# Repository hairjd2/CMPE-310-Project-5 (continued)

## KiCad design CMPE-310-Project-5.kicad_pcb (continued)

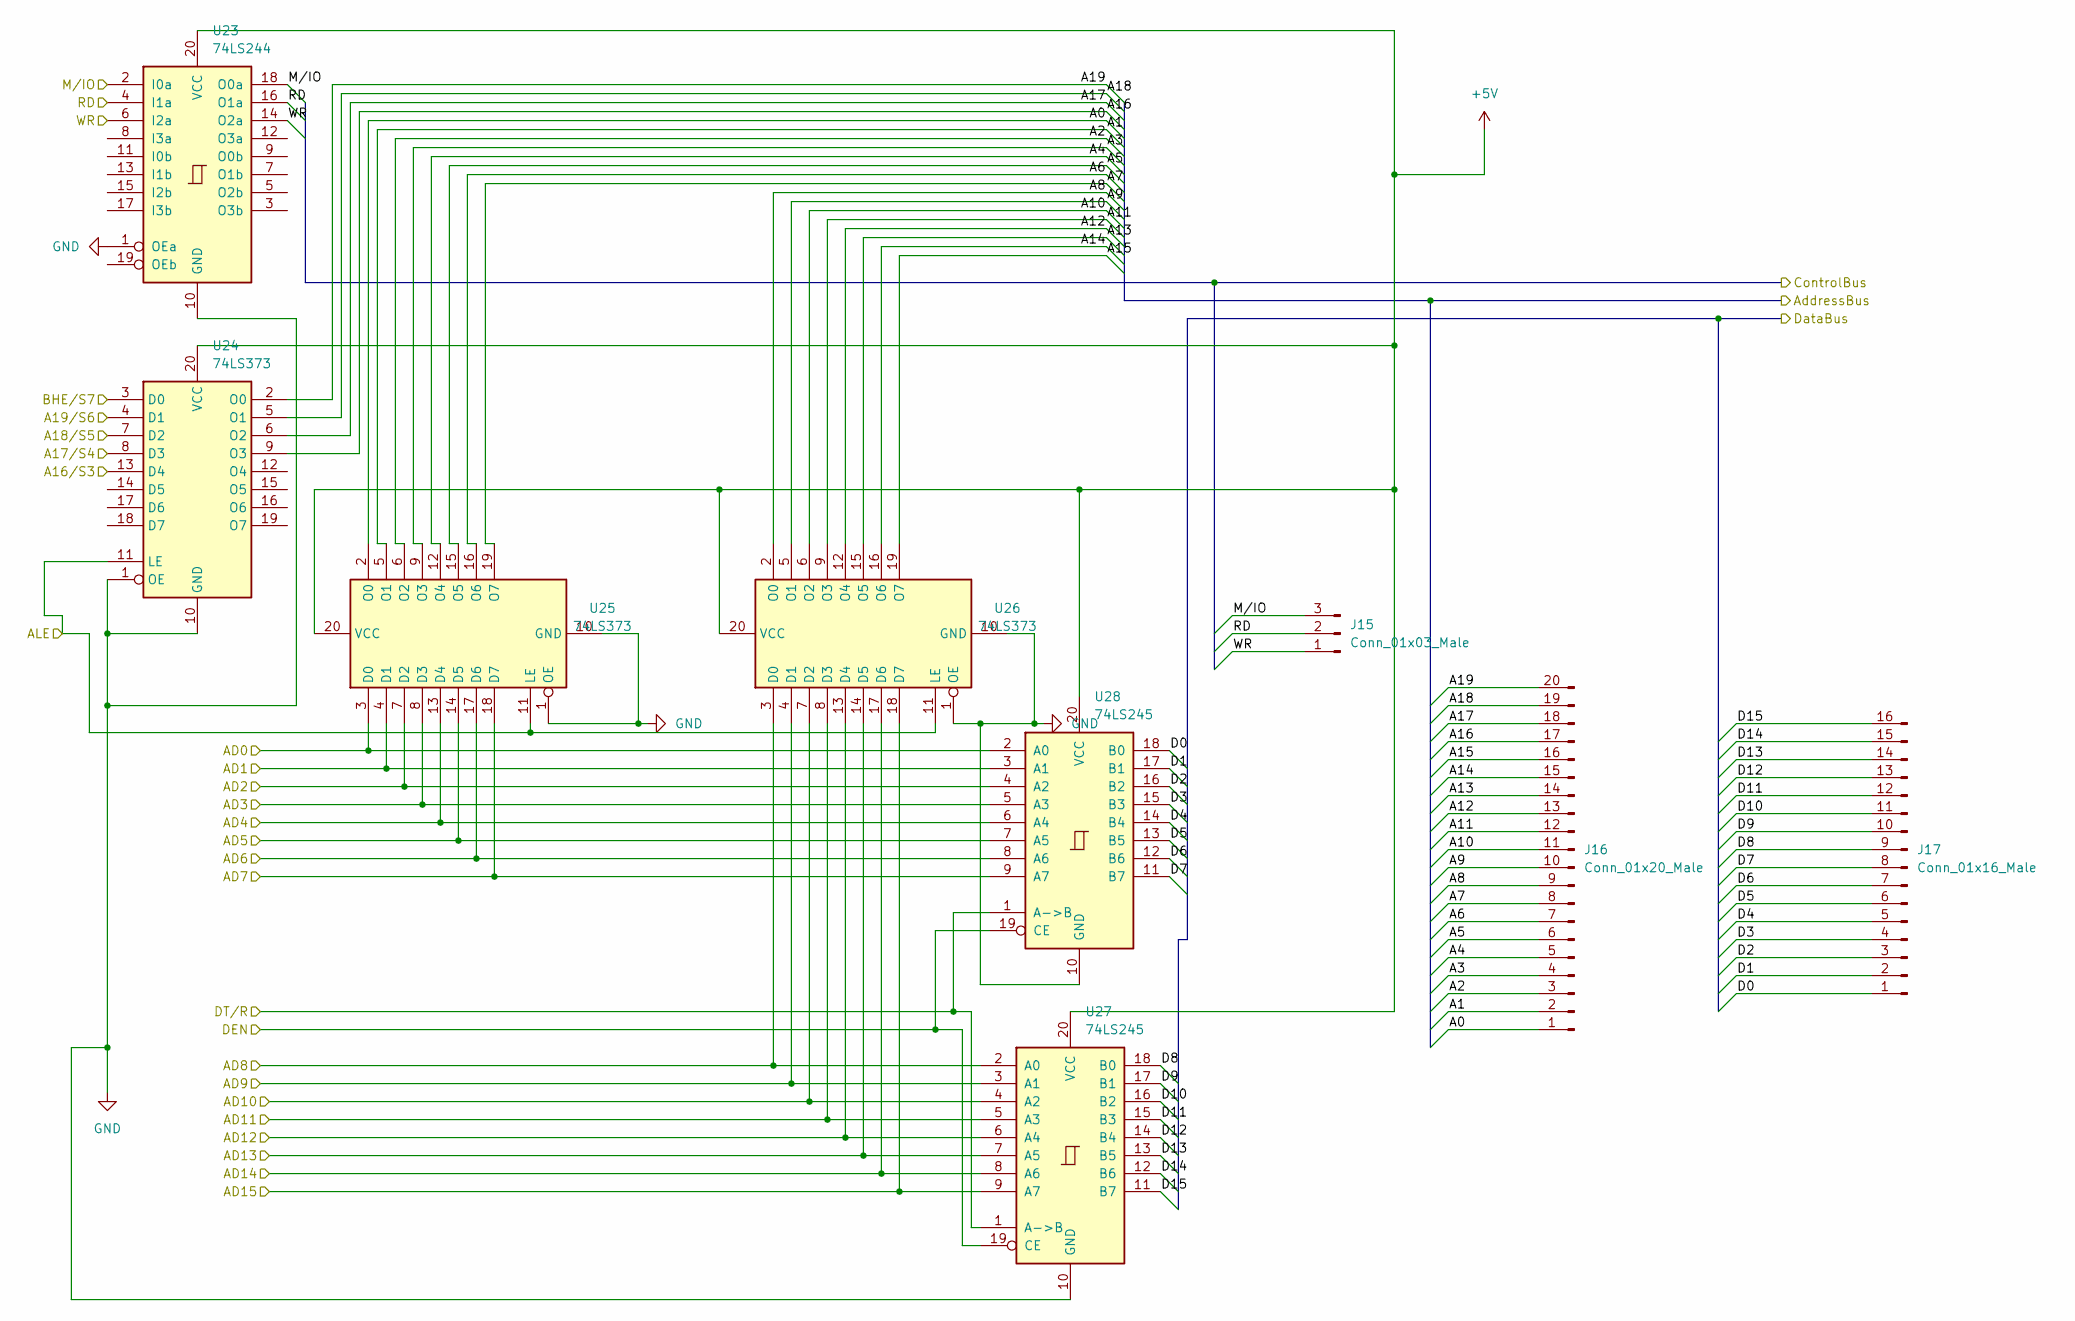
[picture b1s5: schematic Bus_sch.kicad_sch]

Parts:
J15: Conn_01x03_Male; FanPinHeader_1x03_P2.54mm_Vertical
J16: Conn_01x20_Male
J17: Conn_01x16_Male
U23: 74LS244; DIP-20_W7.62mm
U24, U25, U26: 74LS373; DIP-20_W7.62mm
U27, U28: 74LS245; DIP-20_W7.62mm

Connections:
+5V: U23.20 (VCC), U24.20 (VCC), U25.20 (VCC), U26.20 (VCC), U27.20 (VCC), U28.20 (VCC); also elsewhere on the board
/Bus_wires/A0: J16.1, U25.2 (O0)
/Bus_wires/A1: J16.2, U25.5 (O1)
/Bus_wires/A2: J16.3, U25.6 (O2)
/Bus_wires/A3: J16.4, U25.9 (O3)
/Bus_wires/A4: J16.5, U25.12 (O4)
/Bus_wires/A5: J16.6, U25.15 (O5)
/Bus_wires/A6: J16.7, U25.16 (O6)
/Bus_wires/A7: J16.8, U25.19 (O7)
/Bus_wires/A8: J16.9, U26.2 (O0)
/Bus_wires/A9: J16.10, U26.5 (O1)
/Bus_wires/A10: J16.11, U26.6 (O2)
/Bus_wires/A11: J16.12, U26.9 (O3)
/Bus_wires/A12: J16.13, U26.12 (O4)
/Bus_wires/A13: J16.14, U26.15 (O5)
/Bus_wires/A14: J16.15, U26.16 (O6)
/Bus_wires/A15: J16.16, U26.19 (O7)
/Bus_wires/A16: J16.17, U24.9 (O3)
/Bus_wires/A16/S3: U24.13 (D4); also elsewhere on the board
/Bus_wires/A17: J16.18, U24.6 (O2)
/Bus_wires/A17/S4: U24.8 (D3); also elsewhere on the board
/Bus_wires/A18: J16.19, U24.5 (O1)
/Bus_wires/A19: J16.20, U24.2 (O0)
/Bus_wires/AD1: U25.4 (D1), U28.3 (A1); also elsewhere on the board
/Bus_wires/AD2: U25.7 (D2), U28.4 (A2); also elsewhere on the board
/Bus_wires/AD3: U25.8 (D3), U28.5 (A3); also elsewhere on the board
/Bus_wires/AD4: U25.13 (D4), U28.6 (A4); also elsewhere on the board
/Bus_wires/AD5: U25.14 (D5), U28.7 (A5); also elsewhere on the board
/Bus_wires/AD6: U25.17 (D6), U28.8 (A6); also elsewhere on the board
/Bus_wires/AD7: U25.18 (D7), U28.9 (A7); also elsewhere on the board
/Bus_wires/AD8: U26.3 (D0), U27.2 (A0); also elsewhere on the board
/Bus_wires/AD9: U26.4 (D1), U27.3 (A1); also elsewhere on the board
/Bus_wires/AD10: U26.7 (D2), U27.4 (A2); also elsewhere on the board
/Bus_wires/AD11: U26.8 (D3), U27.5 (A3); also elsewhere on the board
/Bus_wires/AD12: U26.13 (D4), U27.6 (A4); also elsewhere on the board
/Bus_wires/AD13: U26.14 (D5), U27.7 (A5); also elsewhere on the board
/Bus_wires/AD14: U26.17 (D6), U27.8 (A6); also elsewhere on the board
/Bus_wires/AD15: U26.18 (D7), U27.9 (A7); also elsewhere on the board
/Bus_wires/ALE: U24.11 (LE), U25.11 (LE), U26.11 (LE); also elsewhere on the board
/Bus_wires/BHE/S7: U24.3 (D0); also elsewhere on the board
/Bus_wires/D0: J17.1, U28.18 (B0)
/Bus_wires/D1: J17.2, U28.17 (B1)
/Bus_wires/D2: J17.3, U28.16 (B2)
/Bus_wires/D3: J17.4, U28.15 (B3)
/Bus_wires/D4: J17.5, U28.14 (B4)
/Bus_wires/D5: J17.6, U28.13 (B5)
/Bus_wires/D6: J17.7, U28.12 (B6)
/Bus_wires/D7: J17.8, U28.11 (B7)
/Bus_wires/D8: J17.9, U27.18 (B0)
/Bus_wires/D9: J17.10, U27.17 (B1)
/Bus_wires/D10: J17.11, U27.16 (B2)
/Bus_wires/D11: J17.12, U27.15 (B3)
/Bus_wires/D12: J17.13, U27.14 (B4)
/Bus_wires/D13: J17.14, U27.13 (B5)
/Bus_wires/D14: J17.15, U27.12 (B6)
/Bus_wires/D15: J17.16, U27.11 (B7)
/Bus_wires/DEN: U27.19 (CE), U28.19 (CE); also elsewhere on the board
/Bus_wires/DT/R: U27.1 (A->B), U28.1 (A->B); also elsewhere on the board
/Bus_wires/RD: J15.2, U23.4 (I1a), U23.16 (O1a); also elsewhere on the board
/Bus_wires/WR: J15.1, U23.6 (I2a), U23.14 (O2a); also elsewhere on the board
/CMOS_wires/A0: U25.3 (D0), U28.2 (A0); also elsewhere on the board
/CMOS_wires/A18: U24.7 (D2); also elsewhere on the board
/CMOS_wires/A19: U24.4 (D1); also elsewhere on the board
/MRDC: J15.3, U23.2 (I0a), U23.18 (O0a); also elsewhere on the board
GND: U23.1 (OEa), U23.10 (GND), U24.1 (OE), U24.10 (GND), U25.1 (OE), U25.10 (GND), U26.1 (OE), U26.10 (GND), U27.10 (GND), U28.10 (GND); also elsewhere on the board

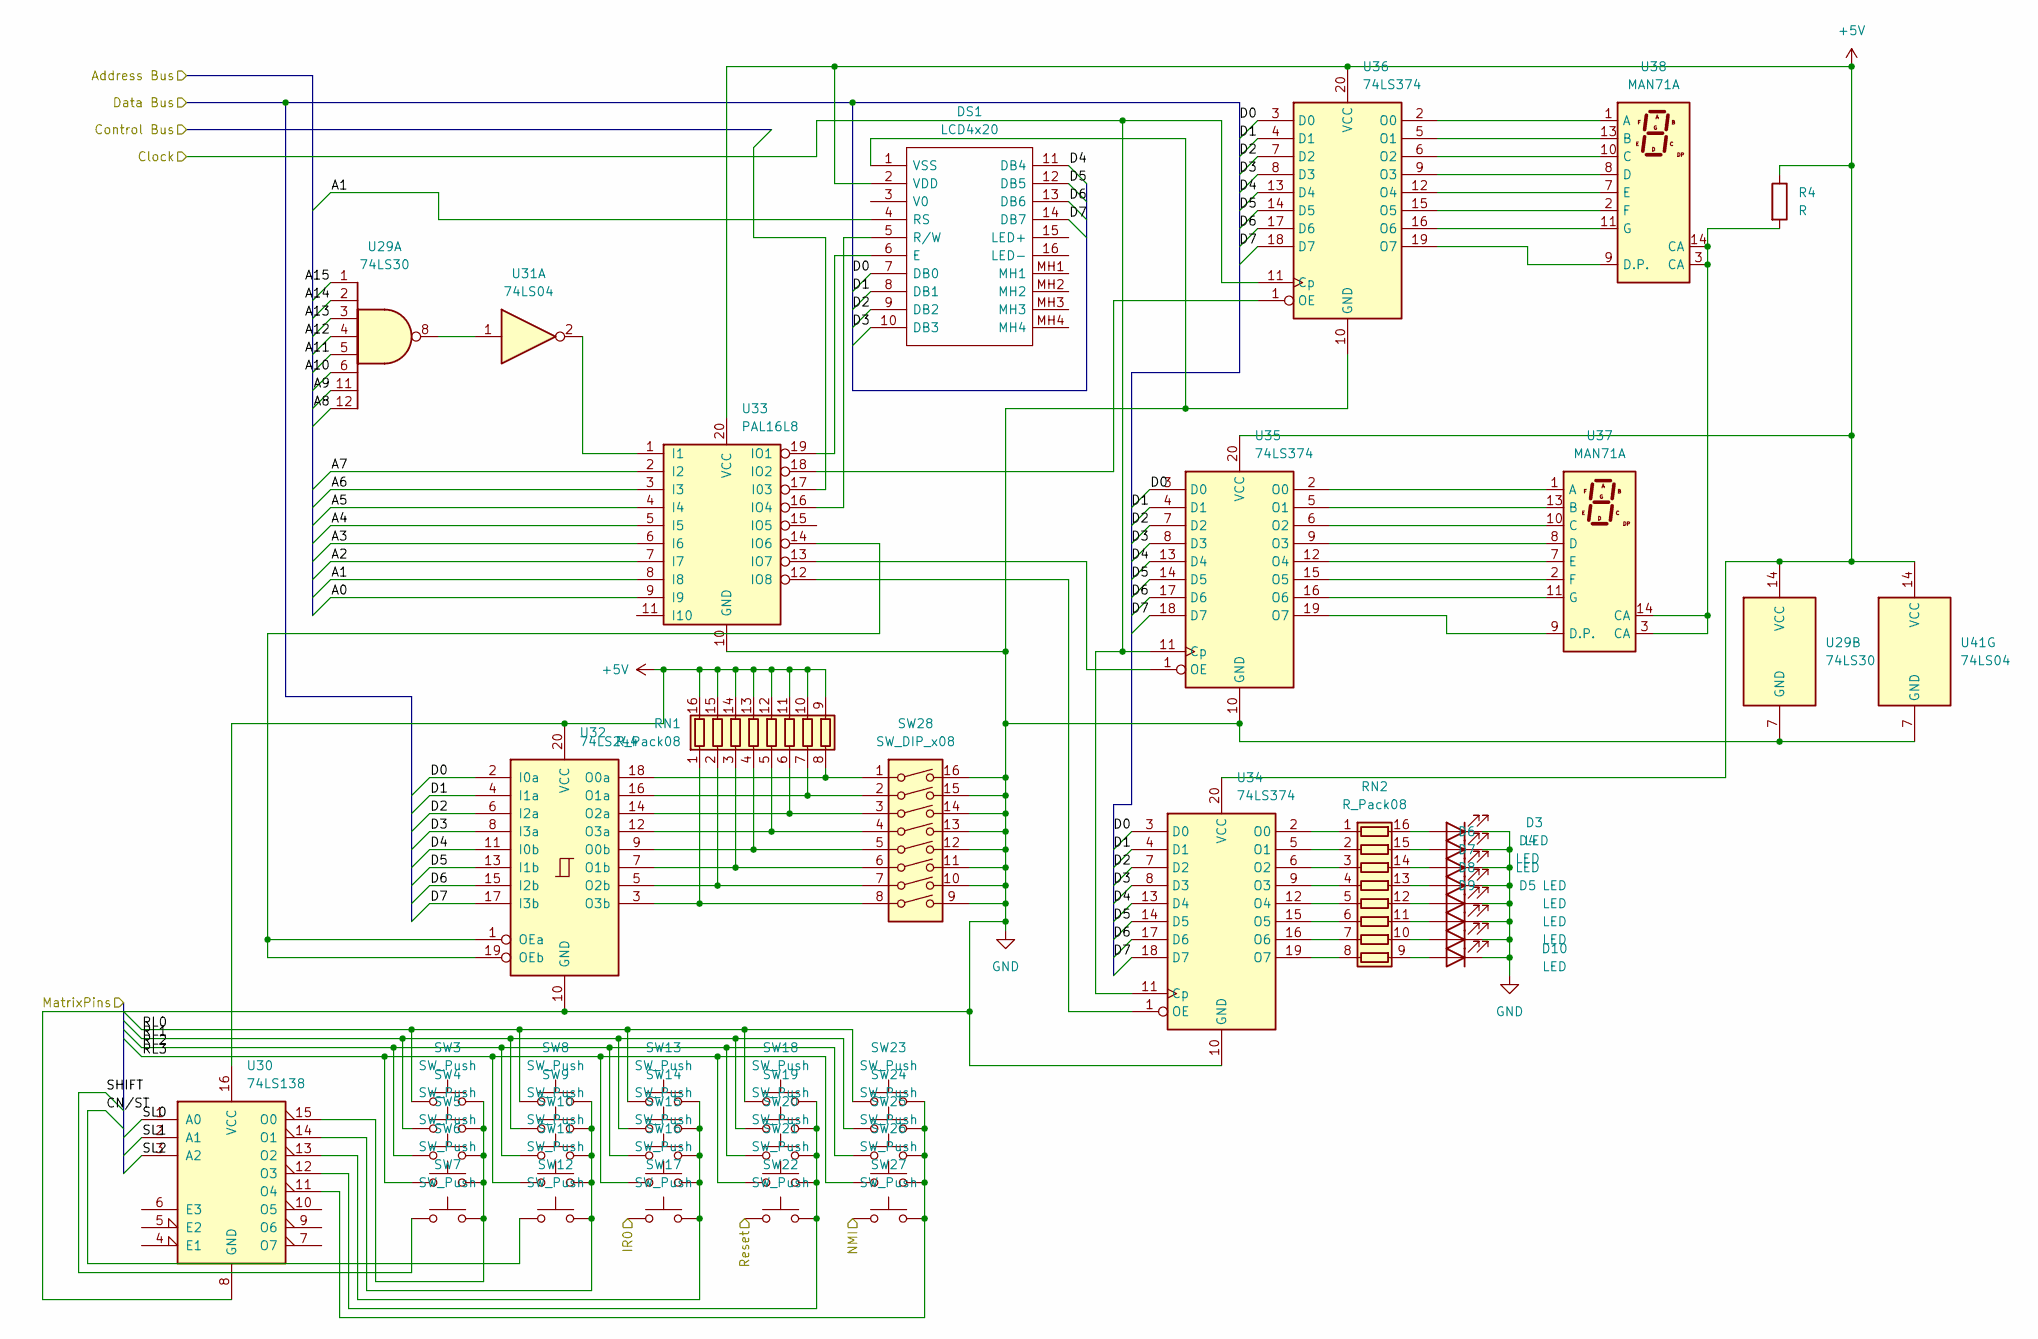
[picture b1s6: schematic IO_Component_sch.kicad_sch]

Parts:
D3, D4, D5, D6, D7, D8, D9, D10: LED; LED_0201_0603Metric
DS1: LCD4x20; Mouser Part Number 763-0420AZFLYBW33V3
R4: R
RN1, RN2: R_Pack08
SW3, SW4, SW5, SW6, SW7, SW8, SW9, SW10, SW11, SW12, SW13, SW14, SW15, SW16, SW17, SW18, SW19, SW20, SW21, SW22, SW23, SW24, SW25, SW26, SW27: SW_Push; SW_Cherry_MX_1.00u_PCB
SW28: SW_DIP_x08; DIN41612_D_2x8_Female_Vertical_THT
U29: 74LS30; PowerIntegrations_eDIP-12B
U30: 74LS138; DIP-16_W7.62mm
U31, U41: 74LS04; DIP-14_W7.62mm
U32: 74LS244; DIP-20_W7.62mm
U33: PAL16L8; DIP-20_W7.62mm
U34, U35, U36: 74LS374; DIP-20_W7.62mm
U37, U38: MAN71A

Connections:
+5V: DS1.2 (VDD), R4.1, RN1.9 (R8.2), RN1.10 (R7.2), RN1.11 (R6.2), RN1.12 (R5.2), RN1.13 (R4.2), RN1.14 (R3.2), RN1.15 (R2.2), RN1.16 (R1.2), U29.14 (VCC), U30.16 (VCC), U32.20 (VCC), U33.20 (VCC), U34.20 (VCC), U35.20 (VCC), U36.20 (VCC), U41.14 (VCC); also elsewhere on the board
/8255_wires/RESET: SW22.1; also elsewhere on the board
/INTR_wires/IO_Component_Wires/A0: U33.9 (I9)
/INTR_wires/IO_Component_Wires/A1: DS1.4 (RS), U33.8 (I8)
/INTR_wires/IO_Component_Wires/A2: U33.7 (I7)
/INTR_wires/IO_Component_Wires/A3: U33.6 (I6)
/INTR_wires/IO_Component_Wires/A4: U33.5 (I5)
/INTR_wires/IO_Component_Wires/A5: U33.4 (I4)
/INTR_wires/IO_Component_Wires/A6: U33.3 (I3)
/INTR_wires/IO_Component_Wires/A7: U33.2 (I2)
/INTR_wires/IO_Component_Wires/A8: U29.12
/INTR_wires/IO_Component_Wires/A9: U29.11
/INTR_wires/IO_Component_Wires/A10: U29.6
/INTR_wires/IO_Component_Wires/A12: U29.4
/INTR_wires/IO_Component_Wires/A13: U29.3
/INTR_wires/IO_Component_Wires/A14: U29.2
/INTR_wires/IO_Component_Wires/A15: U29.1
/INTR_wires/IO_Component_Wires/CN/ST: SW12.1
/INTR_wires/IO_Component_Wires/D0: DS1.7 (DB0), U32.2 (I0a), U34.3 (D0), U35.3 (D0), U36.3 (D0)
/INTR_wires/IO_Component_Wires/D1: DS1.8 (DB1), U32.4 (I1a), U34.4 (D1), U35.4 (D1), U36.4 (D1)
/INTR_wires/IO_Component_Wires/D2: DS1.9 (DB2), U32.6 (I2a), U34.7 (D2), U35.7 (D2), U36.7 (D2)
/INTR_wires/IO_Component_Wires/D3: DS1.10 (DB3), U32.8 (I3a), U34.8 (D3), U35.8 (D3), U36.8 (D3)
/INTR_wires/IO_Component_Wires/D4: DS1.11 (DB4), U32.11 (I0b), U34.13 (D4), U35.13 (D4), U36.13 (D4)
/INTR_wires/IO_Component_Wires/D5: DS1.12 (DB5), U32.13 (I1b), U34.14 (D5), U35.14 (D5), U36.14 (D5)
/INTR_wires/IO_Component_Wires/D6: DS1.13 (DB6), U32.15 (I2b), U34.17 (D6), U35.17 (D6), U36.17 (D6)
/INTR_wires/IO_Component_Wires/D7: DS1.14 (DB7), U32.17 (I3b), U34.18 (D7), U35.18 (D7), U36.18 (D7)
/INTR_wires/IO_Component_Wires/RL0: SW3.1, SW8.1, SW13.1, SW18.1, SW23.1
/INTR_wires/IO_Component_Wires/RL1: SW4.1, SW9.1, SW14.1, SW19.1, SW24.1
/INTR_wires/IO_Component_Wires/RL2: SW5.1, SW10.1, SW15.1, SW20.1, SW25.1
/INTR_wires/IO_Component_Wires/RL3: SW6.1, SW11.1, SW16.1, SW21.1, SW26.1
/INTR_wires/IO_Component_Wires/SHIFT: SW7.1
/INTR_wires/IO_Component_Wires/SL0: U30.1 (A0)
/INTR_wires/IO_Component_Wires/SL1: U30.2 (A1)
/INTR_wires/IO_Component_Wires/SL2: U30.3 (A2)
/INTR_wires/NMI: SW27.1; also elsewhere on the board
/INTR_wires/PCLK: U34.11 (Cp), U35.11 (Cp), U36.11 (Cp); also elsewhere on the board
GND: D3.1 (K), D4.1 (K), D5.1 (K), D6.1 (K), D7.1 (K), D8.1 (K), D9.1 (K), D10.1 (K), DS1.1 (VSS), SW17.1, SW28.9, SW28.10, SW28.11, SW28.12, SW28.13, SW28.14, SW28.15, SW28.16, U29.7 (GND), U30.8 (GND), U32.10 (GND), U33.10 (GND), U34.10 (GND), U35.10 (GND), U36.10 (GND), U41.7 (GND); also elsewhere on the board
unnamed: D3.2 (A), RN2.16 (R1.2)
unnamed: D4.2 (A), RN2.15 (R2.2)
unnamed: D5.2 (A), RN2.14 (R3.2)
unnamed: D6.2 (A), RN2.13 (R4.2)
unnamed: D7.2 (A), RN2.12 (R5.2)
unnamed: D8.2 (A), RN2.11 (R6.2)
unnamed: D9.2 (A), RN2.10 (R7.2)
unnamed: D10.2 (A), RN2.9 (R8.2)
unnamed: DS1.5 (R/W), U33.16 (IO4)
unnamed: DS1.6 (E), U33.19 (IO1)
unnamed: R4.2, U37.3 (CA), U37.14 (CA), U38.3 (CA), U38.12 (NC), U38.14 (CA)
unnamed: RN1.1 (R1.1), SW28.8, U32.3 (O3b)
unnamed: RN1.2 (R2.1), SW28.7, U32.5 (O2b)
unnamed: RN1.3 (R3.1), SW28.6, U32.7 (O1b)
unnamed: RN1.4 (R4.1), SW28.5, U32.9 (O0b)
unnamed: RN1.5 (R5.1), SW28.4, U32.12 (O3a)
unnamed: RN1.6 (R6.1), SW28.3, U32.14 (O2a)
unnamed: RN1.7 (R7.1), SW28.2, U32.16 (O1a)
unnamed: RN1.8 (R8.1), SW28.1, U32.18 (O0a)
unnamed: RN2.1 (R1.1), U34.2 (O0)
unnamed: RN2.2 (R2.1), U34.5 (O1)
unnamed: RN2.3 (R3.1), U34.6 (O2)
unnamed: RN2.4 (R4.1), U34.9 (O3)
unnamed: RN2.5 (R5.1), U34.12 (O4)
unnamed: RN2.6 (R6.1), U34.15 (O5)
unnamed: RN2.7 (R7.1), U34.16 (O6)
unnamed: RN2.8 (R8.1), U34.19 (O7)
unnamed: SW3.2, SW4.2, SW5.2, SW6.2, SW7.2, U30.15 (O0)
unnamed: SW8.2, SW9.2, SW10.2, SW11.2, SW12.2, U30.14 (O1)
unnamed: SW13.2, SW14.2, SW15.2, SW16.2, SW17.2, U30.13 (O2)
unnamed: SW18.2, SW19.2, SW20.2, SW21.2, SW22.2, U30.12 (O3)
unnamed: SW23.2, SW24.2, SW25.2, SW26.2, SW27.2, U30.11 (O4)
unnamed: U29.8, U31.1
unnamed: U31.2, U33.1 (I1)
unnamed: U32.1 (OEa), U32.19 (OEb), U33.14 (IO6)
unnamed: U33.12 (IO8), U34.1 (OE)
unnamed: U33.13 (IO7), U35.1 (OE)
unnamed: U33.18 (IO2), U36.1 (OE)
unnamed: U35.2 (O0), U37.1 (A)
unnamed: U35.5 (O1), U37.13 (B)
unnamed: U35.6 (O2), U37.10 (C)
unnamed: U35.9 (O3), U37.8 (D)
unnamed: U35.12 (O4), U37.7 (E)
unnamed: U35.15 (O5), U37.2 (F)
unnamed: U35.16 (O6), U37.11 (G)
unnamed: U35.19 (O7), U37.9 (D.P.)
unnamed: U36.2 (O0), U38.1 (A)
unnamed: U36.5 (O1), U38.13 (B)
unnamed: U36.6 (O2), U38.10 (C)
unnamed: U36.9 (O3), U38.8 (D)
unnamed: U36.12 (O4), U38.7 (E)
unnamed: U36.15 (O5), U38.2 (F)
unnamed: U36.16 (O6), U38.11 (G)
unnamed: U36.19 (O7), U38.9 (D.P.)

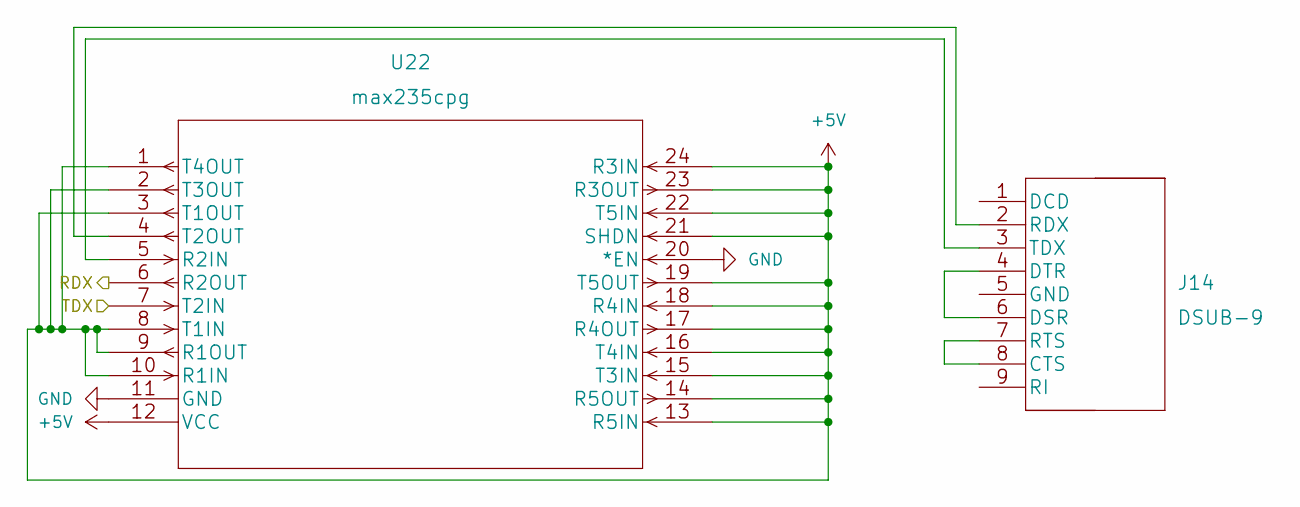
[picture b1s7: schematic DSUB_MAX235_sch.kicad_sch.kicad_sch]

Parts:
J14: DSUB-9
U22: max235cpg

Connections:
+5V: U22.1 (T4OUT), U22.2 (T3OUT), U22.3 (T1OUT), U22.8 (T1IN), U22.9 (R1OUT), U22.10 (R1IN), U22.12 (VCC), U22.13 (R5IN), U22.14 (R5OUT), U22.15 (T3IN), U22.16 (T4IN), U22.17 (R4OUT), U22.18 (R4IN), U22.19 (T5OUT), U22.21 (SHDN), U22.22 (T5IN), U22.23 (R3OUT), U22.24 (R3IN); also elsewhere on the board
/INTR_wires/DSUB_MAX235_wires/RDX: U22.6 (R2OUT); also elsewhere on the board
/INTR_wires/DSUB_MAX235_wires/TDX: U22.7 (T2IN); also elsewhere on the board
GND: U22.11 (GND), U22.20 (*EN); also elsewhere on the board
unnamed: J14.2 (RDX), U22.4 (T2OUT)
unnamed: J14.3 (TDX), U22.5 (R2IN)
unnamed: J14.4 (DTR), J14.6 (DSR)
unnamed: J14.7 (RTS), J14.8 (CTS)

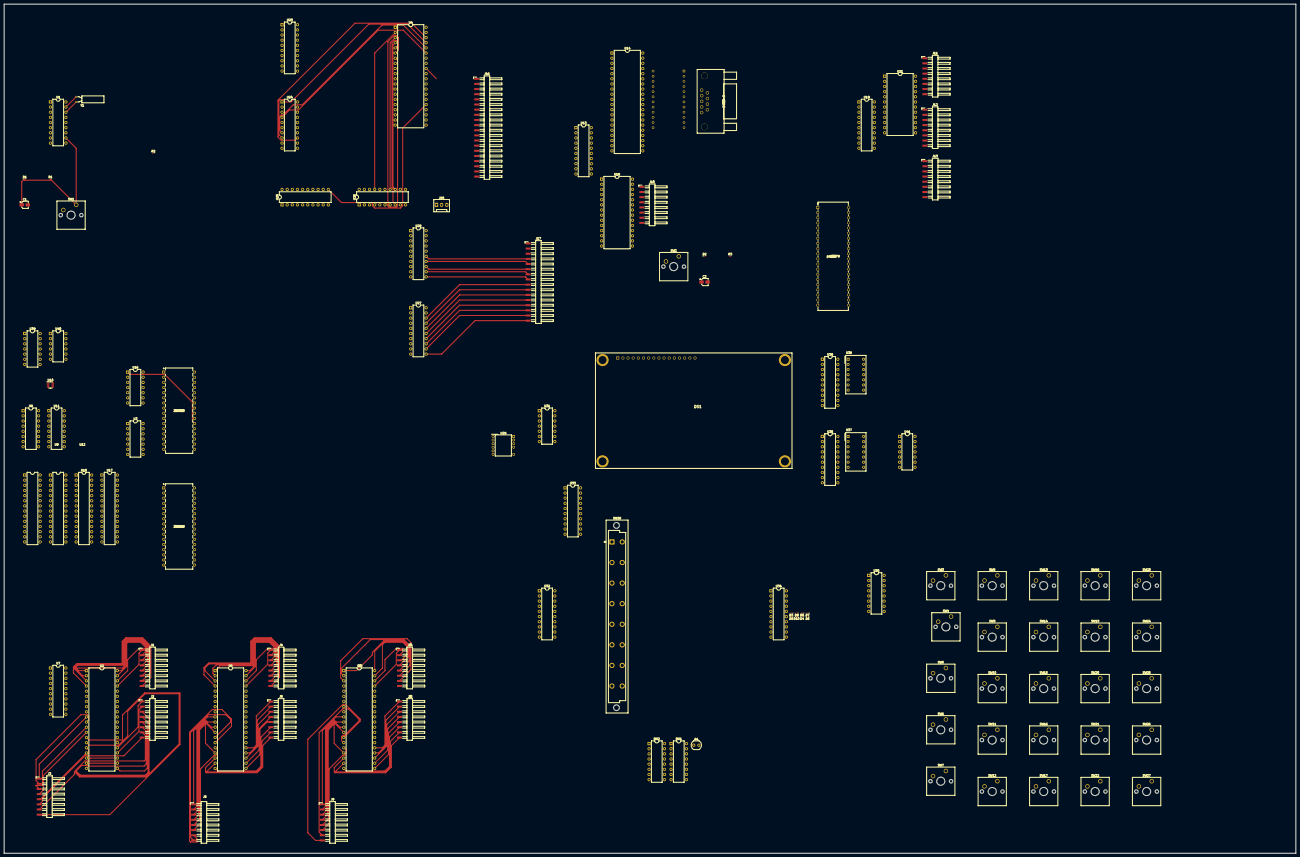
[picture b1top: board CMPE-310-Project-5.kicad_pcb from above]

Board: 8 copper layers, 637.5 x 419.1 mm, 108 parts (1 on the bottom side), 313 nets.

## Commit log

2022-04-23 Created Kicad Directory
2022-04-23 Added components to board. And added missing libs
    Added the 8086, 28F010, DSUB-9, LCD4x20, max235cpg, pkd8279
2022-04-23 Updated PCB from Schematic.
2022-04-23 DSUB-9 moved
2022-04-29 Create CMPE-310-Project-5-2022-04-23_144547.zip
    Added Wiring for the 28F010 (CMOS)
2022-04-29 Created 8255 Sheet
    Created the sheet for the 3 8255's as well as moved the 2 banks into place for the CMOS flash
2022-04-29 PCB Changes
2022-04-29 Updated PCB
    Updated PCB with 8255 sheet
2022-04-29 Updated ZipFile
2022-04-29 Made a quick change to test edits
2022-04-29 More Wiring for the CMOS
2022-04-29 Update .gitignore
    added .zip files
2022-04-29 Added Labeling for CMOS
2022-04-30 File Updates (RAM wired)
2022-04-30 Added new schematic sheets for INTR components
2022-05-03 Wired the UART to the 8259A
2022-05-04 Wired up Decoding of 8255s, 8254, and 8279
    Also fixed up the decoding for the 16550 and the 8259 as well as labeled all wires into/from the bus.
2022-05-05 Wired the max235 and DSUB9
    We will double check the wiring tomorrow. Also added the data bus
2022-05-05 Added Clock Circuit
    Moved the main circuit to the right and added a simple clock generator circuit to the left of the 8086. Still need to wire reset switch
2022-05-05 Added the databus
2022-05-05 Connected 8284 to 8259
2022-05-05 Made reset switch for 8284
2022-05-06 Redid Bus
2022-05-06 Added headers to the necessary pins, and created IO device sheet
    Added headers for the three chips and for the busses. Also created and started to address decode the actual IO components.
2022-05-06 Fixed some wires
2022-05-06 Moved Bus headers
    Moved the bus headers to the sheet with the decoding to save space
2022-05-06 Wired Push Buttons and added footprints
2022-05-06 Added power and ground to chips
    Added power and ground to chips as well as checked and added all labels for pins off of busses
2022-05-06 Enabled inputs on the max235
2022-05-07 Finished wiring and decoding IO devices (except for push button switches)
2022-05-07 Updated PCB
2022-05-09 PCB wiring
2022-05-09 Another change
2022-05-10 Wired 8255 in pcb
2022-05-10 Wired some buses
2022-05-12 More PCB wiring
    Wired all components to eachother, did not interface everything with the 8086
2022-05-13 added some tracks
2022-05-14 Fixed Incorrect Data Pin labels in memory
2022-05-14 MIO Label
